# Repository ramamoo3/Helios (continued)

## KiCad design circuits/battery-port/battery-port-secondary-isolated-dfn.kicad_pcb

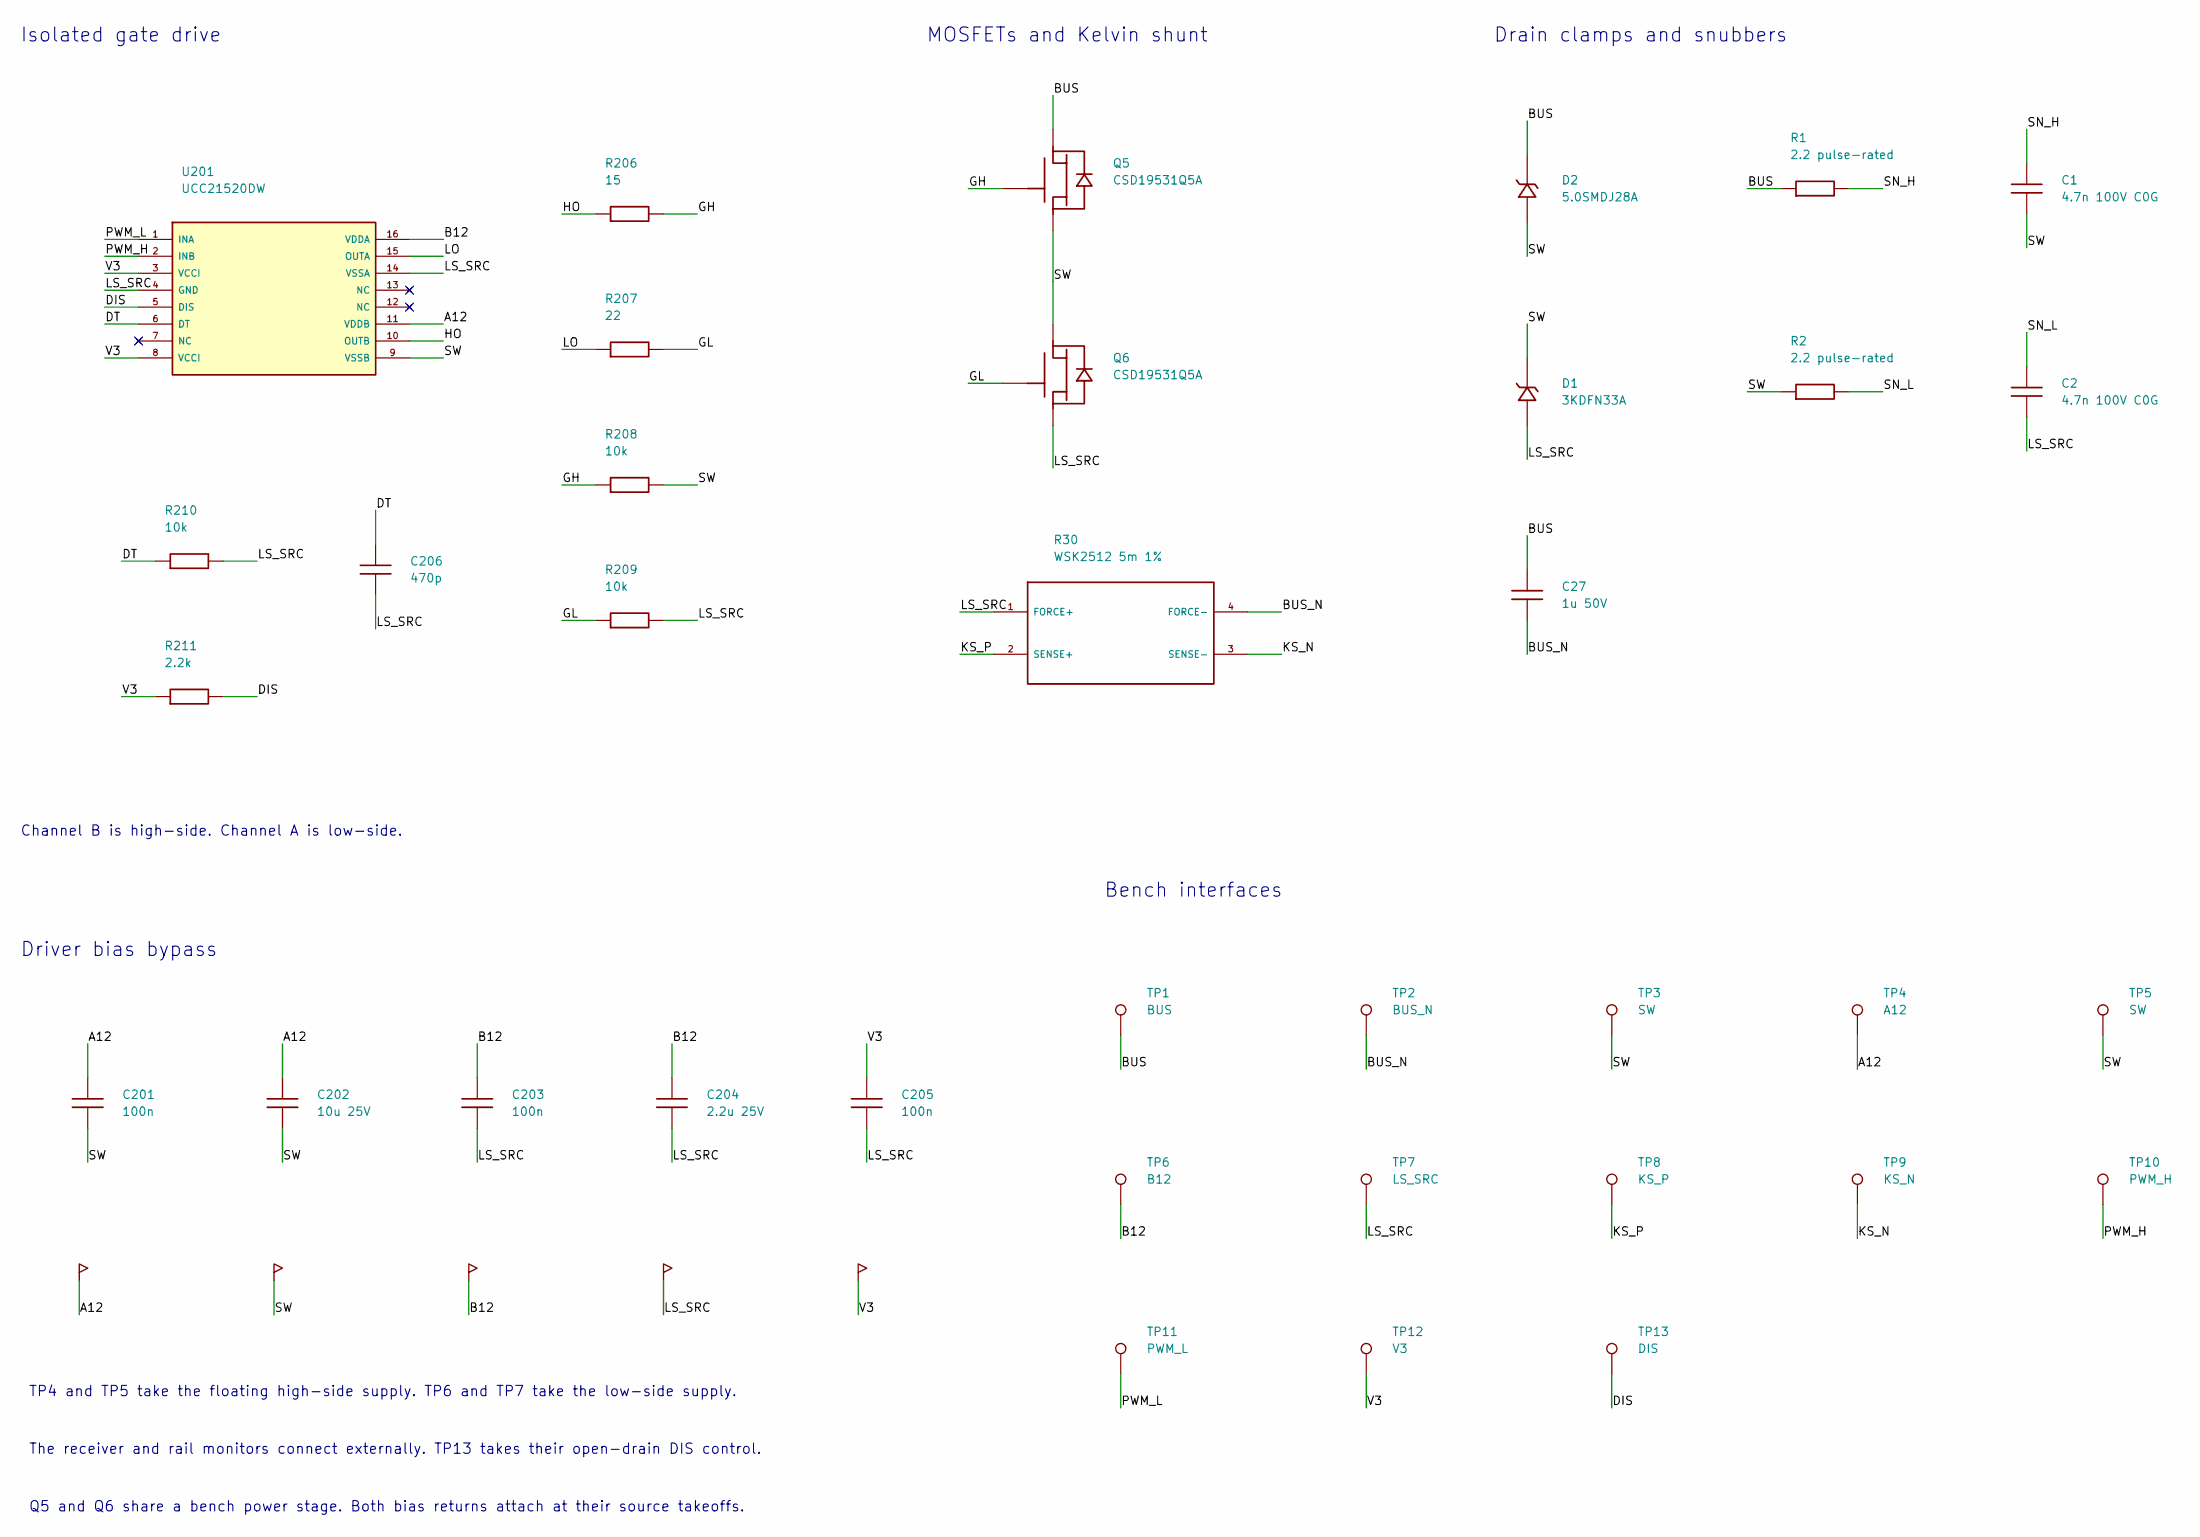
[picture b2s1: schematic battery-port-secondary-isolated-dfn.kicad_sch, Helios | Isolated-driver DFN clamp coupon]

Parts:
C1, C2: 4.7n 100V C0G; C_1206_3216Metric
C27: 1u 50V; C_1206_3216Metric
C201: 100n; C_0402_1005Metric
C202: 10u 25V; C_0805_2012Metric
C203, C205: 100n; C_0603_1608Metric
C204: 2.2u 25V; C_0805_2012Metric
C206: 470p; C_0603_1608Metric
D1: 3KDFN33A; Diode_TVS_Vishay_DFN6546A
D2: 5.0SMDJ28A; D_SMC
Q5, Q6: CSD19531Q5A; VSONP-8-1EP_5x6_P1.27mm
R1, R2: 2.2 pulse-rated; R_1206_3216Metric
R30: WSK2512 5m 1%; Shunt_Vishay_WSK2512_5mR
R206: 15; R_0603_1608Metric
R207: 22; R_0603_1608Metric
R208, R209, R210: 10k; R_0603_1608Metric
R211: 2.2k; R_0603_1608Metric
TP1: BUS; TestPoint_Pad_D3.0mm
TP2: BUS_N; TestPoint_Pad_D3.0mm
TP3: SW; TestPoint_Pad_D3.0mm
TP4: A12; TestPoint_Pad_D1.5mm
TP5: SW; TestPoint_Pad_D1.5mm
TP6: B12; TestPoint_Pad_D1.5mm
TP7: LS_SRC; TestPoint_Pad_D1.5mm
TP8: KS_P; TestPoint_Pad_D1.5mm
TP9: KS_N; TestPoint_Pad_D1.5mm
TP10: PWM_H; TestPoint_Pad_D1.5mm
TP11: PWM_L; TestPoint_Pad_D1.5mm
TP12: V3; TestPoint_Pad_D1.5mm
TP13: DIS; TestPoint_Pad_D1.5mm
U201: UCC21520DW; SOIC-16W_7.5x10.3mm_P1.27mm

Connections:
/A12: C201.1, C202.1, TP4.1, U201.11 (VDDB)
/B12: C203.1, C204.1, TP6.1, U201.16 (VDDA)
/BUS: C27.1, D2.1 (K), Q5.3 (D), R1.1, TP1.1
/BUS_N: C27.2, R30.4 (FORCE-), TP2.1
/DIS: R211.2, TP13.1, U201.5 (DIS)
/DT: C206.1, R210.1, U201.6 (DT)
/GH: Q5.2 (G), R206.2, R208.1
/GL: Q6.2 (G), R207.2, R209.1
/HO: R206.1, U201.10 (OUTB)
/KS_N: R30.3 (SENSE-), TP9.1
/KS_P: R30.2 (SENSE+), TP8.1
/LO: R207.1, U201.15 (OUTA)
/LS_SRC: C2.2, C203.2, C204.2, C205.2, C206.2, D1.2 (A), Q6.1 (S), R30.1 (FORCE+), R209.2, R210.2, TP7.1, U201.4 (GND), U201.14 (VSSA)
/PWM_H: TP10.1, U201.2 (INB)
/PWM_L: TP11.1, U201.1 (INA)
/SN_H: C1.1, R1.2
/SN_L: C2.1, R2.2
/SW: C1.2, C201.2, C202.2, D1.1 (K), D2.2 (A), Q5.1 (S), Q6.3 (D), R2.1, R208.2, TP3.1, TP5.1, U201.9 (VSSB)
/V3: C205.1, R211.1, TP12.1, U201.3 (VCCI), U201.8 (VCCI)

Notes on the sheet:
Isolated gate drive
Channel B is high-side. Channel A is low-side.
MOSFETs and Kelvin shunt
Drain clamps and snubbers
Driver bias bypass
Bench interfaces
TP4 and TP5 take the floating high-side supply. TP6 and TP7 take the low-side supply.
The receiver and rail monitors connect externally. TP13 takes their open-drain DIS control.
Q5 and Q6 share a bench power stage. Both bias returns attach at their source takeoffs.

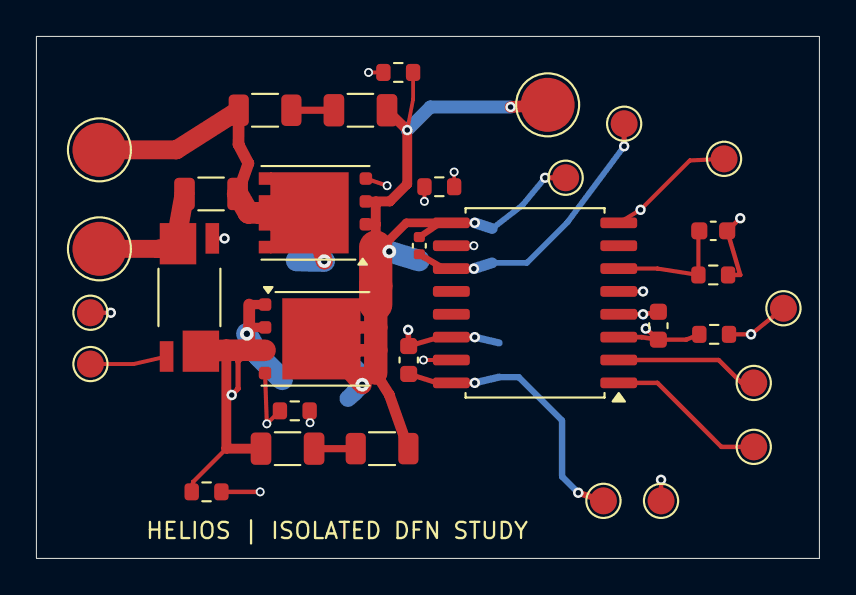
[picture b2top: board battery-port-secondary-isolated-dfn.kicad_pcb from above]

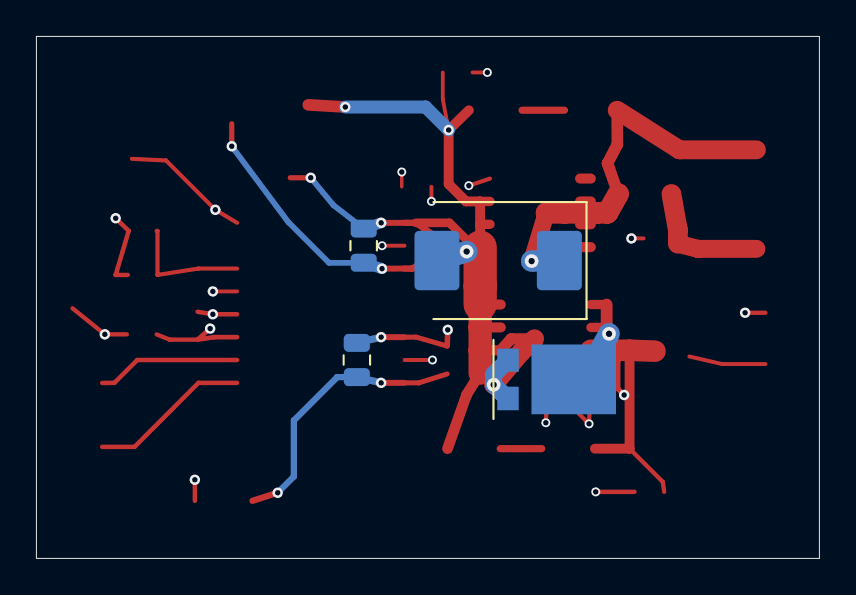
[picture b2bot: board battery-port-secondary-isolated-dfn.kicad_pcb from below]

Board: 4 copper layers, 43.5 x 29.0 mm, 36 parts (4 on the bottom side), 19 nets.

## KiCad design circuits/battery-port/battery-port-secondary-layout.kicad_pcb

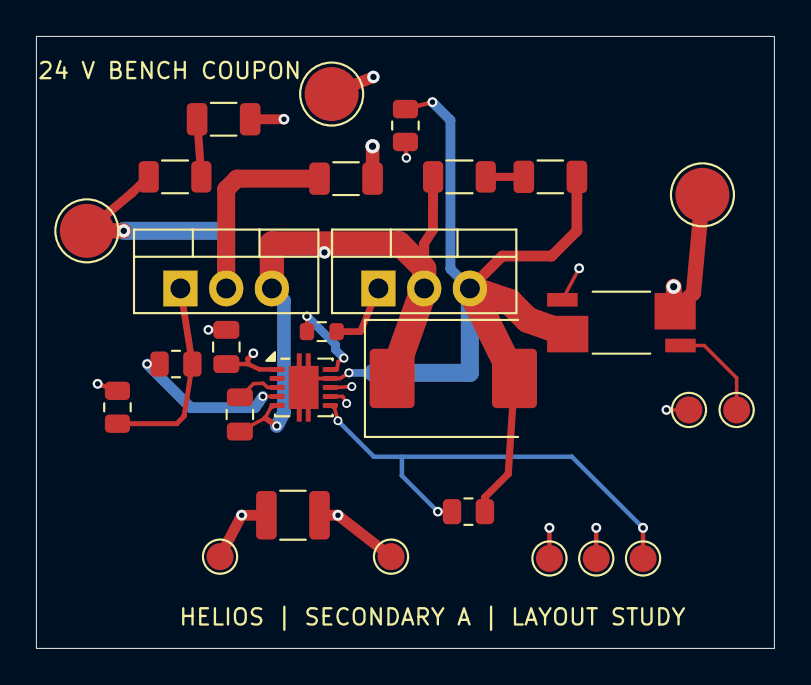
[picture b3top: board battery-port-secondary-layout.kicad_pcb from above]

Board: 4 copper layers, 41.0 x 34.0 mm, 28 parts (0 on the bottom side), 17 nets.

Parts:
C1, C2: 4.7n 100V C0G; C_1206_3216Metric
C27: 1u 50V; C_1206_3216Metric
C204: 100n 25V; C_0805_2012Metric
C205: 22u 25V; C_1210_3225Metric
C206: 100n 50V; C_0805_2012Metric
D1: 5.0SMDJ30A; D_SMC
Q5, Q6: CSD18534KCS; TO-220-3_Vertical
R1, R2: 2.2 pulse rated; R_1206_3216Metric
R30: WSK2512 5m 1%; Shunt_Vishay_WSK2512_5mR
R206: 4.7; R_0805_2012Metric
R207: 4.7; R_0603_1608Metric
R208, R209, R210: 10k; R_0805_2012Metric
TP1: BUS; TestPoint_Pad_D3.0mm
TP2: BUS_N; TestPoint_Pad_D3.0mm
TP3: SW; TestPoint_Pad_D3.0mm
TP4: VDD; TestPoint_Pad_D1.5mm
TP5: LS_SRC; TestPoint_Pad_D1.5mm
TP6: HI; TestPoint_Pad_D1.5mm
TP7: LI; TestPoint_Pad_D1.5mm
TP8: EN; TestPoint_Pad_D1.5mm
TP9: KS_P; TestPoint_Pad_D1.5mm
TP10: KS_N; TestPoint_Pad_D1.5mm
U202: UCC27282DRC; VSON-10-1EP_3x3mm_P0.5mm_EP1.65x2.4mm

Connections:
BOOT: C206.1, U202.3
BUS: C27.1, Q5.2, R1.1, TP1.1
BUS_N: C27.2, R30.4, TP2.1
EN: R210.1, TP8.1, U202.6
GH: Q5.1, R206.2, R208.1
GL: Q6.1, R207.2, R209.1
HI: TP6.1, U202.7
HO: R206.1, U202.4
KS_N: R30.3, TP10.1
KS_P: R30.2, TP9.1
LI: TP7.1, U202.8
LO: R207.1, U202.10
LS_SRC: C2.2, C204.2, C205.2, D1.2, Q6.3, R30.1, R209.2, R210.2, TP5.1, U202.9, U202.11
SN_H: C1.1, R1.2
SN_L: C2.1, R2.2
SW: C1.2, C206.2, D1.1, Q5.3, Q6.2, R2.1, R208.2, TP3.1, U202.5
VDD: C204.1, C205.1, TP4.1, U202.1
